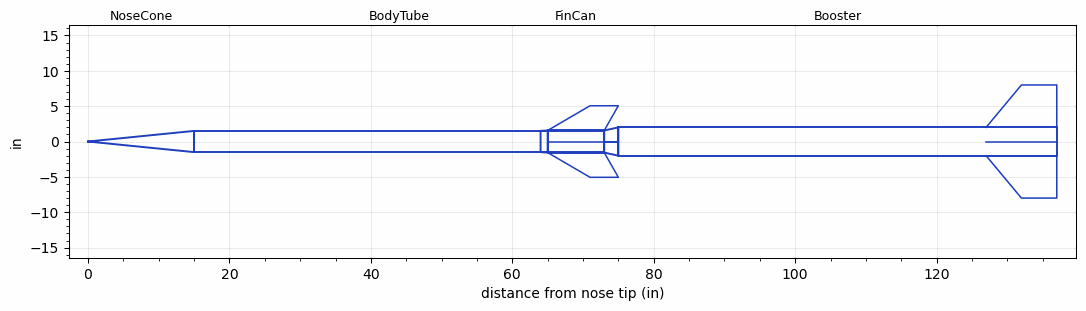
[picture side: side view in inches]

<RASAeroDocument>
 <FileVersion>2</FileVersion>
 <RocketDesign>
  <NoseCone>
   <Length>15</Length>
   <Diameter>3</Diameter>
   <Shape>Conical</Shape>
   <Location>0</Location>
  </NoseCone>
  <BodyTube>
   <Length>58</Length>
   <Diameter>3</Diameter>
   <Location>15</Location>
  </BodyTube>
  <FinCan>
   <Length>8</Length>
   <Diameter>3.125</Diameter>
   <InsideDiameter>3</InsideDiameter>
   <Location>73</Location>
   <ShoulderLength>1</ShoulderLength>
   <Offset>-8</Offset>
   <Fin>
    <Count>4</Count>
    <Chord>8</Chord>
    <Span>3.5</Span>
    <SweepDistance>6</SweepDistance>
    <TipChord>4</TipChord>
    <Thickness>0.187</Thickness>
    <LERadius>0.01</LERadius>
    <Location>8</Location>
    <AirfoilSection>Hexagonal</AirfoilSection>
    <FX1>0.75</FX1>
    <FX3>0.75</FX3>
   </Fin>
  </FinCan>
  <Booster>
   <Length>62</Length>
   <Diameter>4</Diameter>
   <InsideDiameter>3.125</InsideDiameter>
   <RailGuideDiameter>0.7</RailGuideDiameter>
   <RailGuideHeight>0.6</RailGuideHeight>
   <Location>73</Location>
   <ShoulderLength>2</ShoulderLength>
   <Fin>
    <Count>4</Count>
    <Chord>10</Chord>
    <Span>6</Span>
    <SweepDistance>5</SweepDistance>
    <TipChord>5</TipChord>
    <Thickness>0.187</Thickness>
    <LERadius>0.01</LERadius>
    <Location>10</Location>
    <AirfoilSection>Hexagonal</AirfoilSection>
    <FX1>0.75</FX1>
    <FX3>0.75</FX3>
   </Fin>
   <Protuberance>
    <StreamlinedNoBaseDrag>0</StreamlinedNoBaseDrag>
    <StreamlinedWithBaseDrag>0.6</StreamlinedWithBaseDrag>
    <InclinedPlate1Angle>0</InclinedPlate1Angle>
    <InclinedPlate1FrontalArea>0</InclinedPlate1FrontalArea>
    <InclinedPlate2Angle>0</InclinedPlate2Angle>
    <InclinedPlate2FrontalArea>0</InclinedPlate2FrontalArea>
   </Protuberance>
  </Booster>
  <Surface>Rough Camouflage Paint</Surface>
  <ModifiedBarrowman>True</ModifiedBarrowman>
  <Turbulence>True</Turbulence>
  <UseBooster1>False</UseBooster1>
  <UseBooster2>False</UseBooster2>
 </RocketDesign>
 <LaunchSite>
  <Altitude>3700</Altitude>
  <Pressure>29.92</Pressure>
  <RodAngle>1</RodAngle>
  <RodLength>20</RodLength>
  <Temperature>80</Temperature>
  <WindSpeed>5</WindSpeed>
 </LaunchSite>
 <Recovery>
  <Altitude1>1000</Altitude1>
  <Altitude2>1000</Altitude2>
  <DeviceType1>None</DeviceType1>
  <DeviceType2>None</DeviceType2>
  <Event1>False</Event1>
  <Event2>False</Event2>
  <Size1>1</Size1>
  <Size2>1</Size2>
  <EventType1>None</EventType1>
  <EventType2>None</EventType2>
  <CD1>1.33</CD1>
  <CD2>1.33</CD2>
 </Recovery>
 <SimulationList>
  <Simulation>
   <SustainerEngine>3in-N3992  (TsKrush)</SustainerEngine>
   <SustainerLaunchWt>28</SustainerLaunchWt>
   <SustainerNozzleDiameter>2.5</SustainerNozzleDiameter>
   <SustainerCG>47.38</SustainerCG>
   <SustainerIgnitionDelay>10</SustainerIgnitionDelay>
   <Booster1Engine>4in-Current-O7548  (TsKrush)</Booster1Engine>
   <Booster1LaunchWt>64</Booster1LaunchWt>
   <Booster1SeparationDelay>0</Booster1SeparationDelay>
   <Booster1IgnitionDelay>0</Booster1IgnitionDelay>
   <Booster1CG>83.53</Booster1CG>
   <Booster1NozzleDiameter>3.5</Booster1NozzleDiameter>
   <IncludeBooster1>True</IncludeBooster1>
   <Booster2Delay>0</Booster2Delay>
   <IncludeBooster2>False</IncludeBooster2>
   <TimetoApogee>154.5161</TimetoApogee>
   <MaxAltitude>347228.4</MaxAltitude>
   <MaxVelocity>5259.015</MaxVelocity>
  </Simulation>
 </SimulationList>
</RASAeroDocument>
